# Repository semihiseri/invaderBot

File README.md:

# invadeableBot
Working directory for artificial invaders bots

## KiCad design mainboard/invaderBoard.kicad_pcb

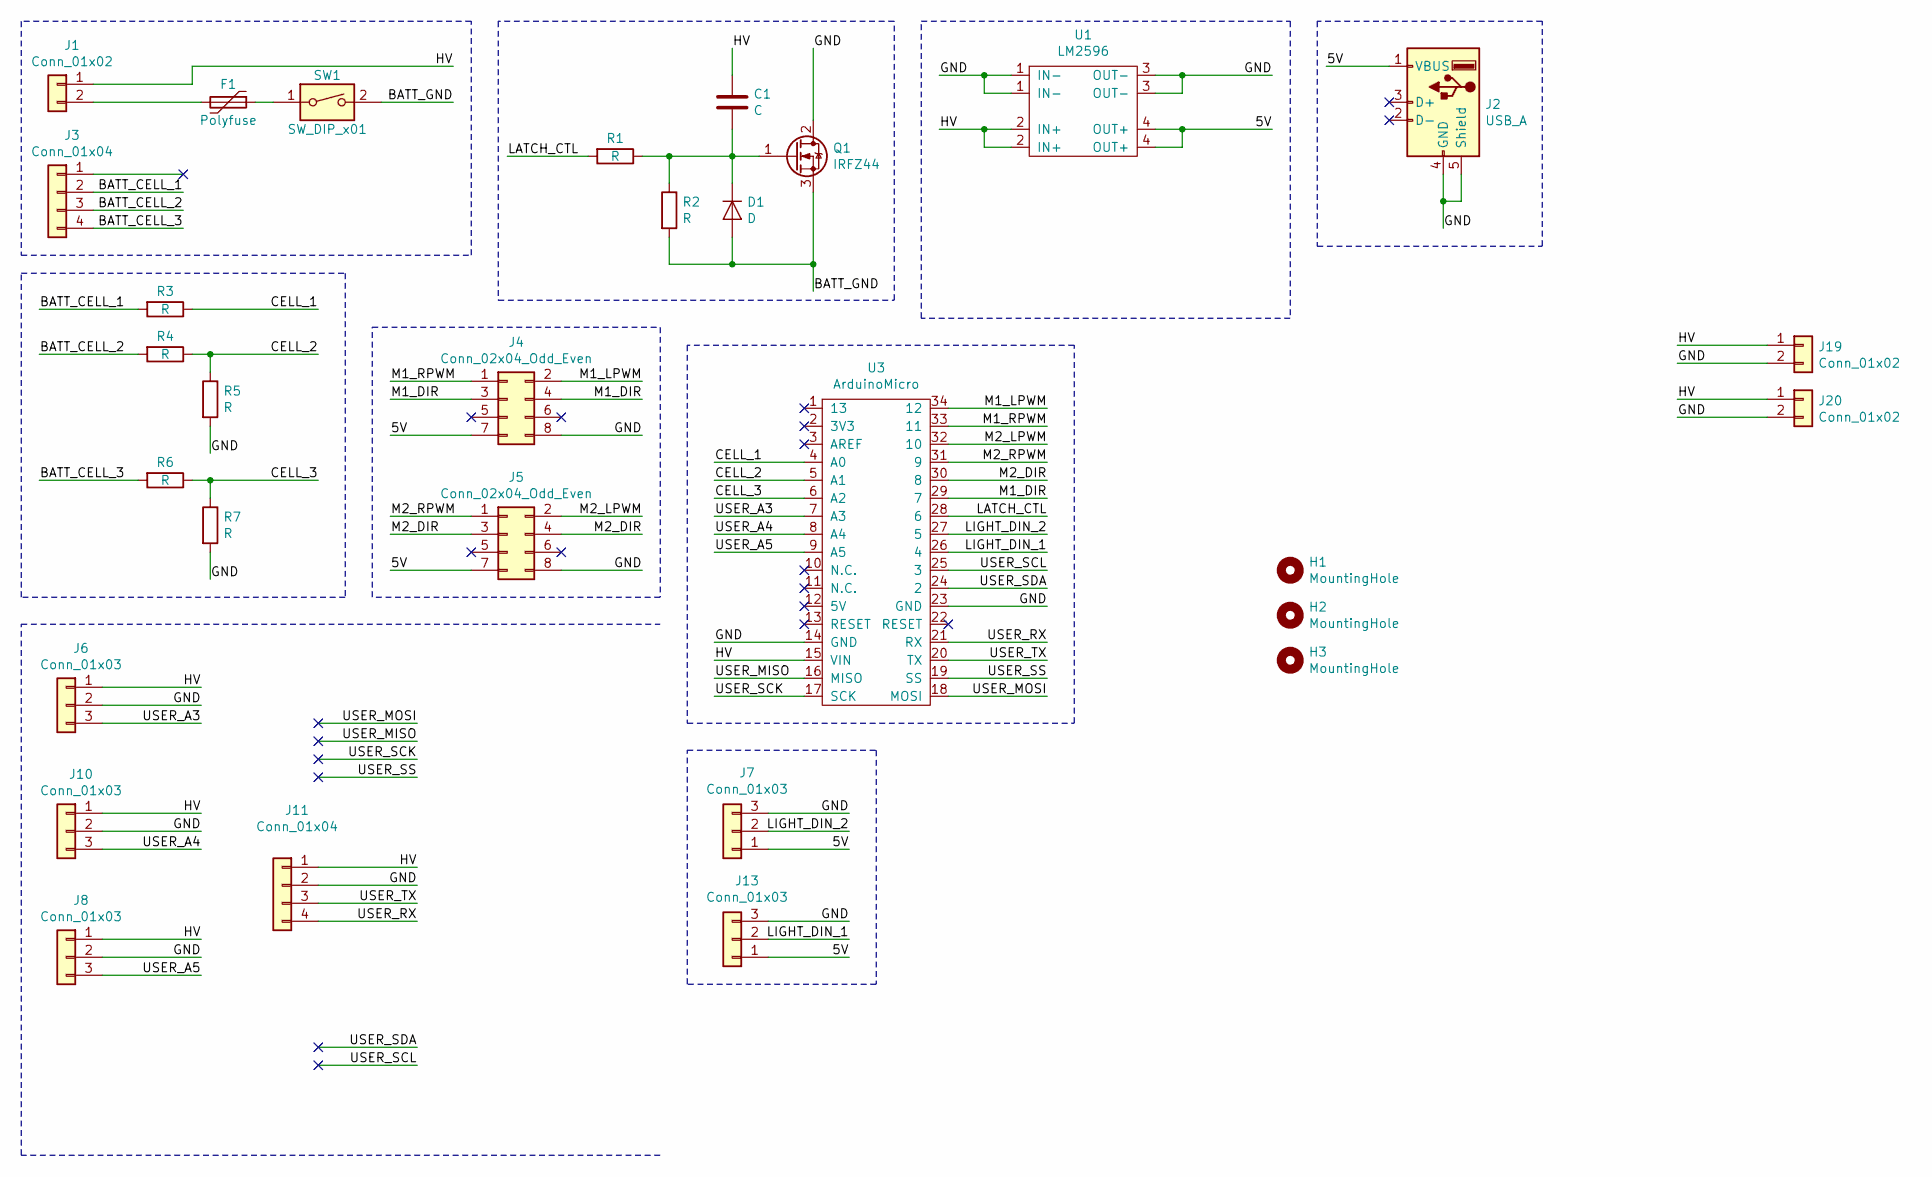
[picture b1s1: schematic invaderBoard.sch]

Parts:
C1: C; CP_Radial_D8.0mm_P2.50mm
D1: D; D_DO-35_SOD27_P7.62mm_Horizontal
F1: Polyfuse; PTC Fuse
H1, H2, H3: MountingHole; MountingHole_3.2mm_M3
J1: Conn_01x02; SolderWirePad_1x02_P7.62mm_Drill2mm
J2: USB_A
J3: Conn_01x04; JST_XH_S4B-XH-A_1x04_P2.50mm_Horizontal
J4, J5: Conn_02x04_Odd_Even; PinHeader_2x04_P2.54mm_Vertical
J6, J7, J8, J10, J13: Conn_01x03; JST_XH_B3B-XH-A_1x03_P2.50mm_Vertical
J11: Conn_01x04; JST_XH_B4B-XH-A_1x04_P2.50mm_Vertical
J19, J20: Conn_01x02; SolderWirePad_1x02_P3.81mm_Drill1mm
Q1: IRFZ44; TO-220-3_Vertical
R1, R2: R; R_Axial_DIN0204_L3.6mm_D1.6mm_P5.08mm_Horizontal
R3, R4, R5, R6, R7: R; R_0805_2012Metric_Pad1.15x1.40mm_HandSolder
SW1: SW_DIP_x01; SolderWirePad_1x02_P3.81mm_Drill1mm
U1: LM2596
U3: ArduinoMicro; Arduino Micro

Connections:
/5V: J2.1 (VBUS), J4.7, J5.7, J7.1, J13.1, U1.4 (OUT+)
/BATT_CELL_1: J3.2, R3.2
/BATT_CELL_2: J3.3, R4.2
/BATT_CELL_3: J3.4, R6.2
/BATT_GND: D1.2 (A), Q1.3 (S), R2.2, SW1.2
/CELL_1: R3.1, U3.4 (A0)
/CELL_2: R4.1, R5.1, U3.5 (A1)
/CELL_3: R6.1, R7.1, U3.6 (A2)
/GND: J2.4 (GND), J2.5 (Shield), J4.8, J5.8, J6.2, J7.3, J8.2, J10.2, J11.2, J13.3, J19.2, J20.2, Q1.2 (D), R5.2, R7.2, U1.1 (IN-), U1.3 (OUT-), U3.14 (GND), U3.23 (GND)
/HV: C1.1, J1.1, J6.1, J8.1, J10.1, J11.1, J19.1, J20.1, U1.2 (IN+), U3.15 (VIN)
/LATCH_CTL: R1.2, U3.28 (6)
/LIGHT_DIN_1: J13.2, U3.26 (4)
/LIGHT_DIN_2: J7.2, U3.27 (5)
/M1_DIR: J4.3, J4.4, U3.29 (7)
/M1_RPWM: J4.1, U3.33 (11)
/M2_DIR: J5.3, J5.4, U3.30 (8)
/M2_LPWM: J5.2, U3.32 (10)
/M2_RPWM: J5.1, U3.31 (9)
/USER_A3: J6.3, U3.7 (A3)
/USER_A4: J10.3, U3.8 (A4)
/USER_A5: J8.3, U3.9 (A5)
/USER_MISO: U3.16 (MISO)
/USER_MOSI: U3.18 (MOSI)
/USER_RX: J11.4, U3.21 (RX)
/USER_SCK: U3.17 (SCK)
/USER_SCL: U3.25 (3)
/USER_SDA: U3.24 (2)
/USER_SS: U3.19 (SS)
/USER_TX: J11.3, U3.20 (TX)
unnamed: C1.2, D1.1 (K), Q1.1 (G), R1.1, R2.1
unnamed: F1.1, SW1.1
unnamed: F1.2, J1.2

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
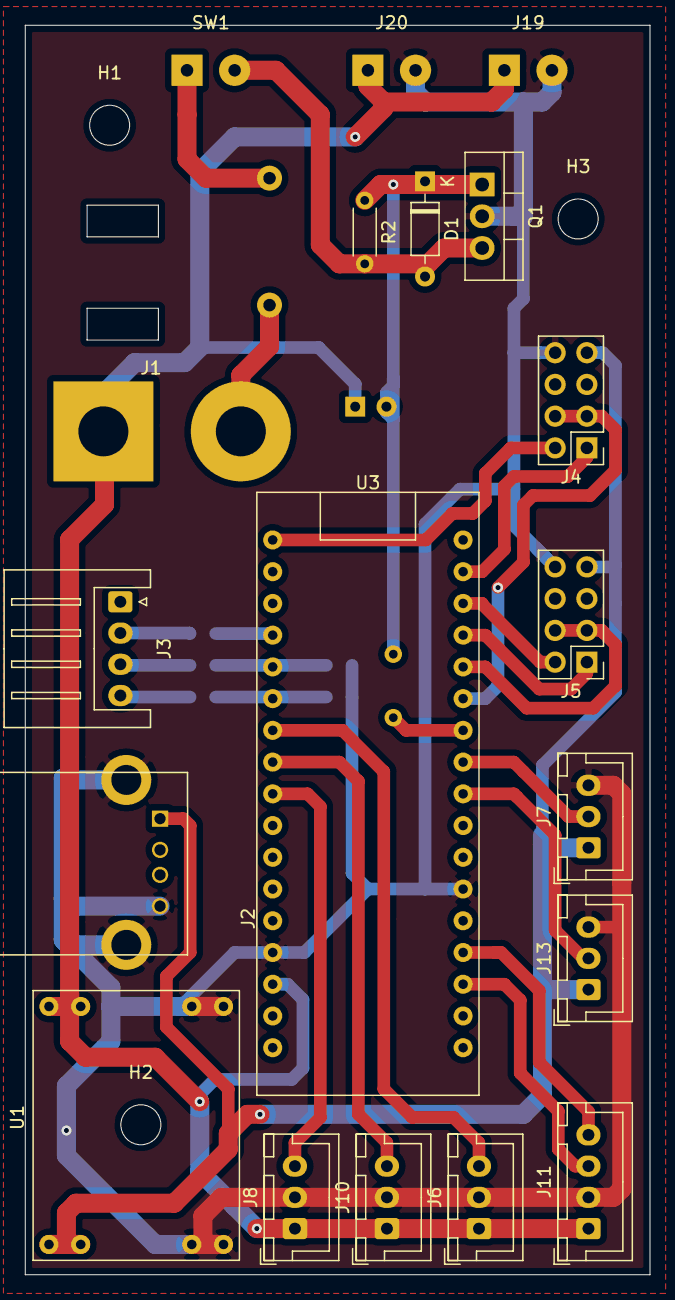
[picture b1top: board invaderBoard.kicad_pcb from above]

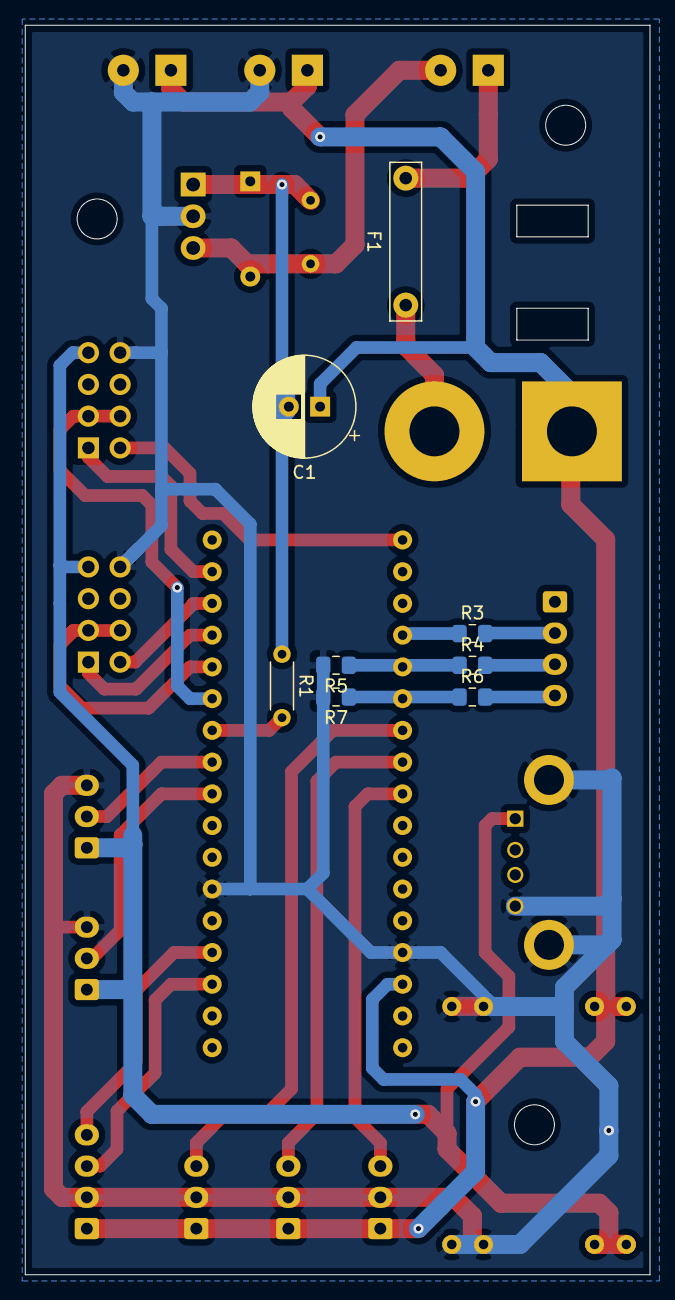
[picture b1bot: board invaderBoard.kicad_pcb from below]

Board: 2 copper layers, 50.0 x 100.0 mm, 30 parts (8 on the bottom side), 27 nets.

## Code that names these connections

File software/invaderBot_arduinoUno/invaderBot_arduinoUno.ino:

//const int CELL_1 = A0;
//const int CELL_2 = A1;
//const int CELL_3 = A2;

//              13, 11, 10, 9
//int pinPwm[] = { 0,  0,  0, 0};

//                  R L
int motorSpeed[] = {0,0};

void motorTask()
{
  if (motorSpeed[0] >= 0)
  {
    analogWrite(9, motorSpeed[0]);
    digitalWrite(4, HIGH);
    digitalWrite(5, LOW);
  }

  if (motorSpeed[0] < 0)
  {
    analogWrite(9, abs(motorSpeed[0]));
    digitalWrite(4, LOW);
    digitalWrite(5, HIGH);
  }

  // ------------------
  
  if (motorSpeed[1] >= 0)
  {
    analogWrite(10, motorSpeed[1]);
    digitalWrite(7, HIGH);
    digitalWrite(8, LOW);
  }

  if (motorSpeed[1] < 0)
  {
    analogWrite(10, abs(motorSpeed[1]));
    digitalWrite(7, LOW);
    digitalWrite(8, HIGH);
  }

  // ------------------
  
  /*if (pinPwm[0] != pinPwm[1]) // Safety
  {
    pinPwm[0] = 0;
    pinPwm[1] = 0;
  }
  if (pinPwm[2] != pinPwm[3]) // Safety
  {
    pinPwm[2] = 0;
    pinPwm[3] = 0;
  }*/

  Serial.print(motorSpeed[0]);
  Serial.print(" ");
  Serial.print(motorSpeed[1]);
  Serial.println(" ");
}

/*void batteryTask()
{
  int c1, c2, c3;
  c1 = analogRead(CELL_1)*5; // an approximation. The range 0mV:5000mV corresponds to 0:1024 on default ADC resolution (10-bits)
  c2 = analogRead(CELL_2)*5; // an approximation. So 5000/1024 is somewhat like 5. It is a simpler calculation and good enough!
  c3 = analogRead(CELL_3)*5; // an approximation.

  c2 = c2*2-c1;
  c3 = c3*3-c2-c1;

  Serial.print("B=");
  Serial.print(c1);
  Serial.print(",");
  Serial.print(c2);
  Serial.print(",");
  Serial.println(c3);

  if (true)
  {
    digitalWrite(6, HIGH);
  }
}*/

void setup() {
  Serial.begin(9600);
  
  // Motor Driver;
 // Motor_1 controll pin initiate;
 pinMode(4, OUTPUT);     
 pinMode(5, OUTPUT);    
 pinMode(9, OUTPUT); // Speed control
 
 // Motor_2 controll pin initiate;
 pinMode(7, OUTPUT);     
 pinMode(8, OUTPUT);    
 pinMode(10, OUTPUT);  // Speed control
 
 //Enable the Motor Shield output;  
 pinMode(6, OUTPUT); 
 digitalWrite(6, HIGH);  
 
  delay(100);

  // Battery Monitor;
//  batteryTask();
}

void loop() {
  char firstChar;
  int value;

  // batteryTask();
  
  if (Serial.available())
  {
    firstChar = Serial.read();

    if (firstChar == 'R' || 
        firstChar == 'L' ||
        firstChar == 'C')
    {
      value = Serial.parseInt();
      if (value > 255 || value < -255)
      {
        value = 0;
      }
    }
    else if(firstChar == 'G')
    {
      motorTask();
    }
  /*  else if(firstChar == 'B')
    {
      batteryTask();
    }*/

    switch (firstChar)
    {
      case 'R': // Right Motor
        motorSpeed[0] = value;
        break;
      case 'L': // Left Motor
        motorSpeed[1] = value;
        break;
      case 'C':
        Serial.print("MUST_INVADE_");
        Serial.println(value*value); // Check code.
      default:
        break;
    }

    // motorTask();
  }

  // delay(100);

  return;
}

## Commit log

2019-04-06 track
    print in place track
2019-04-27 initial loadblock
2019-04-27 track and wheel stuf added
2019-04-28 files from old version -> tensioner and D coupling
2019-04-28 new tensioner
2019-04-28 fixed interference between track and slider
2019-04-29 invaderboard initial commit
2019-04-30 kicad version 5 update
2019-05-01 Motor coupling doned
2019-05-16 first working combination
2019-05-20 Notes to PCB design
2019-07-23 Mainboard schematics mostly done
2019-07-24 PCB mostly done, motor power outputs added to schematics
2019-08-04 Updated PCB - layout done, routing isn't
2019-08-04 a new cube added
2019-08-05 PCB Done, some changes on schematics
2019-08-05 PCB holes added + capacitor simulator in LTspice
2019-08-15 Manuf files created
2019-08-29 some changes I guess
2019-08-29 arduino FW added + some changes on sch.
2019-08-29 basic keyboardcontroller
2019-09-03 PCB updated -v1 finalized
2019-09-06 Docs added
2019-09-15 Some more changes
2019-09-15 improved arduino code
2019-09-16 Obsolete drawings removed
2019-09-16 More obsolete drawings removed
2019-09-17 drill tool added
2019-09-17 drill tool modification
2019-09-19 driveWheel3 + more documentation
2019-10-02 Tubeholder added and maybe 1-2 more things
2019-10-03 Battery level can be retrieved via arduino. Also robot-going-crazy is fixed in kbctl
2019-10-12 firmware for alternative arduino uno solution added
